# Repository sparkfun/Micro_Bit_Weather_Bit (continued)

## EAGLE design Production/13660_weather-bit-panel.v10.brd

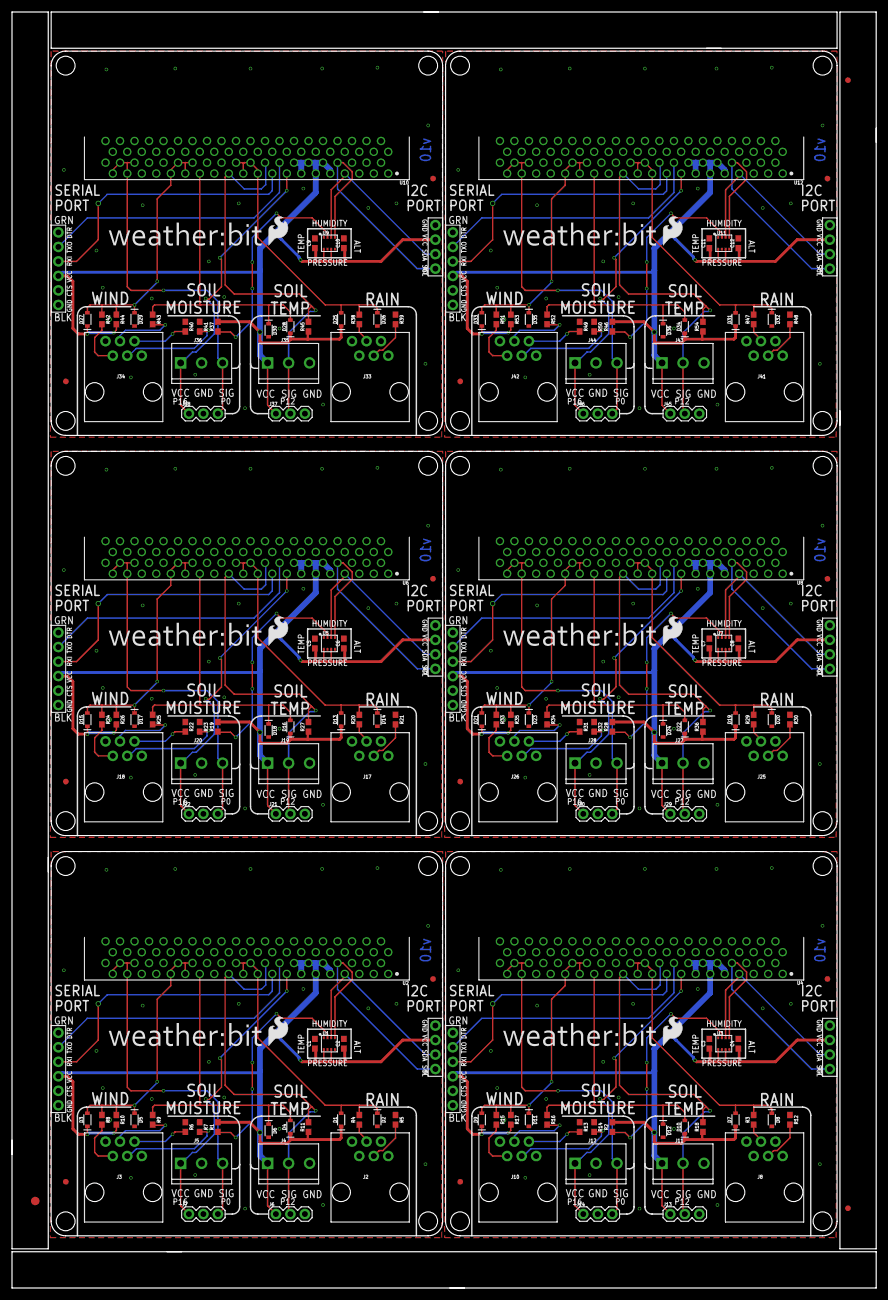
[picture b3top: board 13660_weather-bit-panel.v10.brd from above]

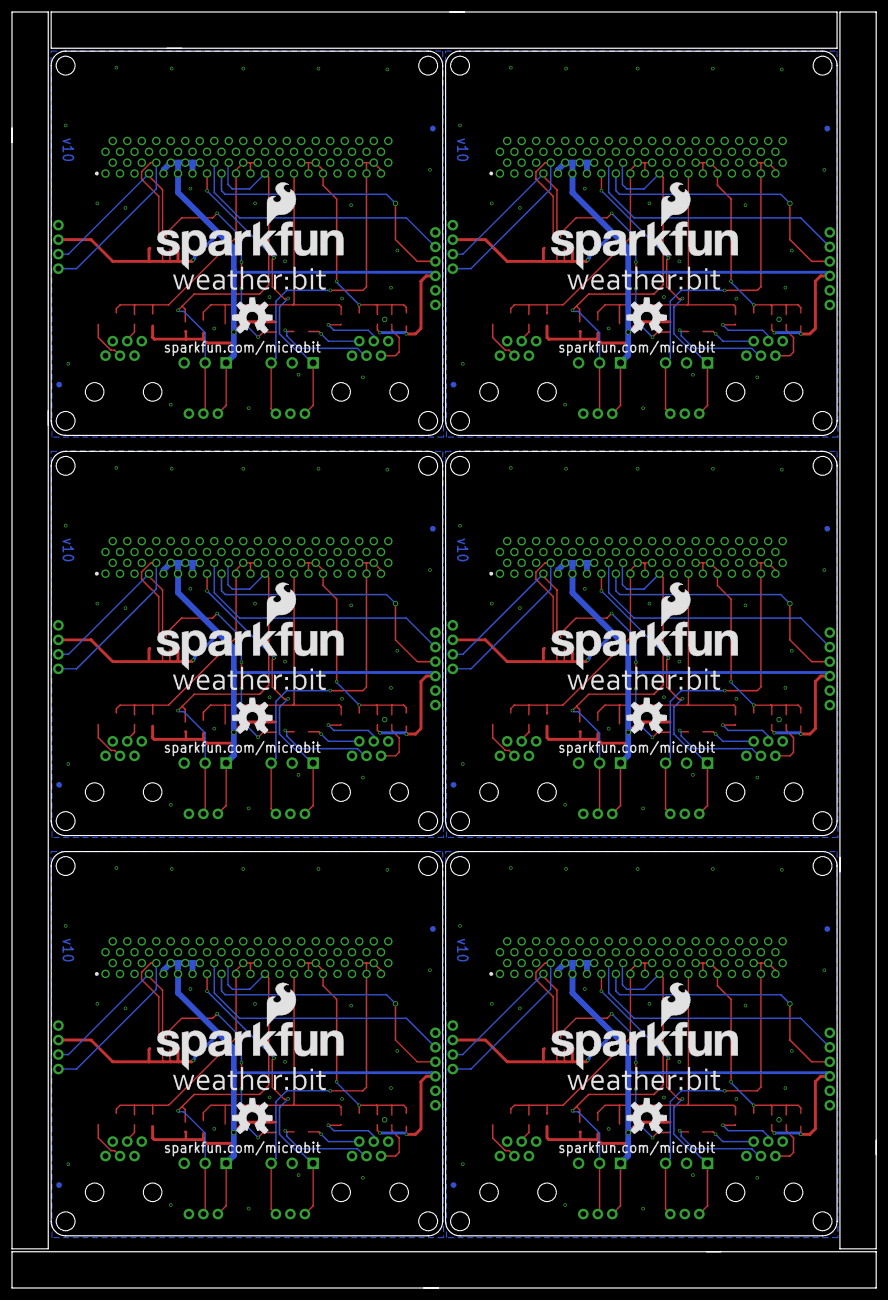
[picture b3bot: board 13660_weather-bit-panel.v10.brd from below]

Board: 2 copper layers, 151.4 x 223.5 mm, 243 parts (30 on the bottom side), 114 nets.

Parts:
C1, C2, C3, C4, C5, C6, C7, C8, C9, C10, C11, C12: 0.1uF; 0603
D1, D2, D3, D4, D5, D6, D7, D8, D9, D10, D11, D12, D13, D14, D15, D16, D17, D18, D19, D20, D21, D22, D23, D24, D25, D26, D27, D28, D29, D30, D31, D32, D33, D34, D35, D36: 250mA/100V; SOD-323
E$1: FIDUCIAL-1.5X3
E$7, E$8: FIDUCIAL-1X2
FD1, FD2, FD3, FD4, FD5, FD6, FD7, FD8, FD9, FD10, FD11, FD12, FD13, FD14, FD15, FD16, FD17, FD18, FD19, FD20, FD21, FD22, FD23, FD24: FIDUCIAL1X2; FIDUCIAL-1X2
H1, H2, H3, H4, H5, H6, H7, H8, H9, H10, H11, H12, H13, H14, H15, H16, H17, H18, H19, H20, H21, H22, H23, H24: STAND-OFF
J1, J16, J24, J32, J40, J48: 6_PIN_SERIAL_TARGET_SIDE_W_SILK
J2, J3, J8, J10, J17, J18, J25, J26, J33, J34, J41, J42: RJ11; RJ11-6
J4, J5, J11, J12, J19, J20, J27, J28, J35, J36, J43, J44: SCREWTERMINAL-3.5MM-3_LOCK.007S
J6, J7, J13, J14, J21, J22, J29, J30, J37, J38, J45, J46: 1X03
J9, J15, J23, J31, J39, J47: 1X04_NO_SILK
LOGO1, LOGO3, LOGO5, LOGO7, LOGO9, LOGO11: OSHW-LOGOL; OSHW-LOGO-L
LOGO2, LOGO4, LOGO6, LOGO8, LOGO10, LOGO12: SFE_LOGO_NAME_FLAME.3_INCH; SFE_LOGO_NAME_FLAME_.3
R1, R2, R10, R11, R17, R18, R19, R26, R27, R28, R35, R36, R37, R44, R45, R46, R53, R54: 4.7k; 0603
R3, R4, R5, R6, R7, R8, R9, R12, R13, R14, R15, R16, R20, R21, R22, R23, R24, R25, R29, R30, R31, R32, R33, R34, R38, R39, R40, R41, R42, R43, R47, R48, R49, R50, R51, R52: 1k; 0603
U1, U3, U5, U7, U9, U11: BME280; LGA-8-2.5X2.5
U2, U4, U6, U8, U10, U12: micro:bit; MICRO:BIT_RA_PTH
U$1, U$4, U$7, U$10, U$13, U$16: SFE_LOGO_FLAME_.2
U$2, U$3, U$5, U$6, U$8, U$9, U$11, U$12, U$14, U$15, U$17, U$18: LOGO-WEATHERBIT

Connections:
3.3V: C1.1, C2.1, D1.C, D3.C, D4.C, J1.P$4, J4.1, J6.1, J9.3, R1.2, R10.2, R11.1, U1.6, U1.8, U2.A9, U2.A10, U2.A11, U2.A12, U2.A13, U2.A14
3.3V1: C3.1, C4.1, D7.C, D9.C, D10.C, J11.1, J13.1, J15.3, J16.P$4, R2.2, R17.2, R18.1, U3.6, U3.8, U4.A9, U4.A10, U4.A11, U4.A12, U4.A13, U4.A14
3.3V2: C5.1, C6.1, D13.C, D15.C, D16.C, J19.1, J21.1, J23.3, J24.P$4, R19.2, R26.2, R27.1, U5.6, U5.8, U6.A9, U6.A10, U6.A11, U6.A12, U6.A13, U6.A14
3.3V3: C7.1, C8.1, D19.C, D21.C, D22.C, J27.1, J29.1, J31.3, J32.P$4, R28.2, R35.2, R36.1, U7.6, U7.8, U8.A9, U8.A10, U8.A11, U8.A12, U8.A13, U8.A14
3.3V4: C9.1, C10.1, D25.C, D27.C, D28.C, J35.1, J37.1, J39.3, J40.P$4, R37.2, R44.2, R45.1, U9.6, U9.8, U10.A9, U10.A10, U10.A11, U10.A12, U10.A13, U10.A14
3.3V5: C11.1, C12.1, D31.C, D33.C, D34.C, J43.1, J45.1, J47.3, J48.P$4, R46.2, R53.2, R54.1, U11.6, U11.8, U12.A9, U12.A10, U12.A11, U12.A12, U12.A13, U12.A14
GND: C1.2, C2.2, D2.A, D5.A, D6.A, J1.P$5, J1.P$6, J4.3, J5.2, J6.3, J7.2, J9.4, R5.1, R6.1, R7.1, U1.1, U1.5, U1.7, U2.A1, U2.A2, U2.A3, U2.A4, U2.A5, U2.A6
GND1: C3.2, C4.2, D8.A, D11.A, D12.A, J11.3, J12.2, J13.3, J14.2, J15.4, J16.P$5, J16.P$6, R12.1, R13.1, R14.1, U3.1, U3.5, U3.7, U4.A1, U4.A2, U4.A3, U4.A4, U4.A5, U4.A6
GND2: C5.2, C6.2, D14.A, D17.A, D18.A, J19.3, J20.2, J21.3, J22.2, J23.4, J24.P$5, J24.P$6, R21.1, R22.1, R23.1, U5.1, U5.5, U5.7, U6.A1, U6.A2, U6.A3, U6.A4, U6.A5, U6.A6
GND3: C7.2, C8.2, D20.A, D23.A, D24.A, J27.3, J28.2, J29.3, J30.2, J31.4, J32.P$5, J32.P$6, R30.1, R31.1, R32.1, U7.1, U7.5, U7.7, U8.A1, U8.A2, U8.A3, U8.A4, U8.A5, U8.A6
GND4: C9.2, C10.2, D26.A, D29.A, D30.A, J35.3, J36.2, J37.3, J38.2, J39.4, J40.P$5, J40.P$6, R39.1, R40.1, R41.1, U9.1, U9.5, U9.7, U10.A1, U10.A2, U10.A3, U10.A4, U10.A5, U10.A6
GND5: C11.2, C12.2, D32.A, D35.A, D36.A, J43.3, J44.2, J45.3, J46.2, J47.4, J48.P$5, J48.P$6, R48.1, R49.1, R50.1, U11.1, U11.5, U11.7, U12.A1, U12.A2, U12.A3, U12.A4, U12.A5, U12.A6
unnamed: R1.1, U1.2
unnamed: R2.1, U3.2
unnamed: J8.3, R3.1
unnamed: J2.3, R4.1
unnamed: J3.2, R8.2
unnamed: J2.4, R5.2
unnamed: J8.4, R12.2
unnamed: J10.3, R16.2
unnamed: J3.3, R9.2
unnamed: J10.5, R13.2
unnamed: J3.5, R6.2
unnamed: J3.4, R7.2
unnamed: J10.4, R14.2
unnamed: J10.2, R15.2
unnamed: R19.1, U5.2
unnamed: J17.3, R20.1
unnamed: J17.4, R21.2
unnamed: J18.3, R25.2
unnamed: J18.5, R22.2
unnamed: J18.4, R23.2
unnamed: J18.2, R24.2
unnamed: R28.1, U7.2
unnamed: J25.3, R29.1
unnamed: J25.4, R30.2
unnamed: J26.3, R34.2
unnamed: J26.5, R31.2
unnamed: J26.4, R32.2
unnamed: J26.2, R33.2
unnamed: R37.1, U9.2
unnamed: J33.3, R38.1
unnamed: J33.4, R39.2
unnamed: J34.3, R43.2
unnamed: J34.5, R40.2
unnamed: J34.4, R41.2
unnamed: J34.2, R42.2
unnamed: R46.1, U11.2
unnamed: J41.3, R47.1
unnamed: J41.4, R48.2
unnamed: J42.3, R52.2
unnamed: J42.5, R49.2
unnamed: J42.4, R50.2
unnamed: J42.2, R51.2
RAIN: D1.A, D2.C, R4.2, U2.A19, U2.A20, U2.A21, U2.A22
RAIN1: D7.A, D8.C, R3.2, U4.A19, U4.A20, U4.A21, U4.A22
RAIN2: D13.A, D14.C, R20.2, U6.A19, U6.A20, U6.A21, U6.A22
RAIN3: D19.A, D20.C, R29.2, U8.A19, U8.A20, U8.A21, U8.A22
RAIN4: D25.A, D26.C, R38.2, U10.A19, U10.A20, U10.A21, U10.A22
RAIN5: D31.A, D32.C, R47.2, U12.A19, U12.A20, U12.A21, U12.A22
RXI: J1.P$3, U2.A17
RXI1: J16.P$3, U4.A17
RXI2: J24.P$3, U6.A17
RXI3: J32.P$3, U8.A17
RXI4: J40.P$3, U10.A17
RXI5: J48.P$3, U12.A17
SCL: J9.1, U1.4, U2.A8
SCL1: J15.1, U3.4, U4.A8
SCL2: J23.1, U5.4, U6.A8
SCL3: J31.1, U7.4, U8.A8
SCL4: J39.1, U9.4, U10.A8
SCL5: J47.1, U11.4, U12.A8
SDA: J9.2, U1.3, U2.A7
SDA1: J15.2, U3.3, U4.A7
SDA2: J23.2, U5.3, U6.A7
SDA3: J31.2, U7.3, U8.A7
SDA4: J39.2, U9.3, U10.A7
SDA5: J47.2, U11.3, U12.A7
SOIL_DAT: J5.3, J7.3, U2.A36, U2.A37, U2.A38, U2.A39
SOIL_DAT1: J12.3, J14.3, U4.A36, U4.A37, U4.A38, U4.A39
SOIL_DAT2: J20.3, J22.3, U6.A36, U6.A37, U6.A38, U6.A39
SOIL_DAT3: J28.3, J30.3, U8.A36, U8.A37, U8.A38, U8.A39
SOIL_DAT4: J36.3, J38.3, U10.A36, U10.A37, U10.A38, U10.A39
SOIL_DAT5: J44.3, J46.3, U12.A36, U12.A37, U12.A38, U12.A39
SOIL_PWR: J5.1, J7.1, U2.A15
SOIL_PWR1: J12.1, J14.1, U4.A15
SOIL_PWR2: J20.1, J22.1, U6.A15
SOIL_PWR3: J28.1, J30.1, U8.A15
SOIL_PWR4: J36.1, J38.1, U10.A15
SOIL_PWR5: J44.1, J46.1, U12.A15
TEMP_DAT: J4.2, J6.2, R11.2, U2.A18, U2.A23
TEMP_DAT1: J11.2, J13.2, R18.2, U4.A18, U4.A23
TEMP_DAT2: J19.2, J21.2, R27.2, U6.A18, U6.A23
TEMP_DAT3: J27.2, J29.2, R36.2, U8.A18, U8.A23
TEMP_DAT4: J35.2, J37.2, R45.2, U10.A18, U10.A23
TEMP_DAT5: J43.2, J45.2, R54.2, U12.A18, U12.A23
TXO: J1.P$2, U2.A16
TXO1: J16.P$2, U4.A16
TXO2: J24.P$2, U6.A16
TXO3: J32.P$2, U8.A16
TXO4: J40.P$2, U10.A16
TXO5: J48.P$2, U12.A16
WDIR: D3.A, D5.C, R8.1, R10.1, U2.A28, U2.A29, U2.A30, U2.A31
WDIR1: D9.A, D11.C, R15.1, R17.1, U4.A28, U4.A29, U4.A30, U4.A31
WDIR2: D15.A, D17.C, R24.1, R26.1, U6.A28, U6.A29, U6.A30, U6.A31
WDIR3: D21.A, D23.C, R33.1, R35.1, U8.A28, U8.A29, U8.A30, U8.A31
WDIR4: D27.A, D29.C, R42.1, R44.1, U10.A28, U10.A29, U10.A30, U10.A31
WDIR5: D33.A, D35.C, R51.1, R53.1, U12.A28, U12.A29, U12.A30, U12.A31
WSPEED: D4.A, D6.C, R9.1, U2.A27
WSPEED1: D10.A, D12.C, R16.1, U4.A27
WSPEED2: D16.A, D18.C, R25.1, U6.A27
WSPEED3: D22.A, D24.C, R34.1, U8.A27
WSPEED4: D28.A, D30.C, R43.1, U10.A27
WSPEED5: D34.A, D36.C, R52.1, U12.A27

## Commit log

2017-03-20 Initial Commit to set up repo
2017-03-23 Sch and Brd files initial commit
2017-03-27 Updated Baord Layout, prepping for today's meeting
2017-03-29 Updated brd and sch file 3/28/2017
2017-03-29 updated board and sch files 3/29
2017-03-30 Adding Library Part Updated Brd File Updated Sch File 3/30/2017
2017-04-03 Updated BRD and SCH files per Design Review 3/31
2017-04-06 Updated brd and sch files per QC Review
2017-04-10 Updated BRD and SCH files per EDU
2017-04-11 replacing proportional font back to vector font
2017-04-18 updated weather:bit Logo
2017-04-18 Updated logo info
2017-04-20 Updated silk per review 4/19
2017-05-23 Updated One-Wire Hardware Set-up
2017-05-31 Updating weather:bit per QC review
2017-05-31 Updated text in sch
2017-05-31 panel
2017-07-21 updating file structure for product release - adding notes to readme
2019-01-08 micro:arcade Example Code HEX files
    Add compiled MakeCode example code used in kit.
2019-02-08 Update microbit-Weather-Bit-Experiment-7-OpenLog.hex
    Updated code with button press to begin logging and to pause logging. It's a hex file but you can still import it in MakeCode to view code.
2019-02-08 Update microbit-Weather-Bit-Experiment-7-OpenLog.hex
    Update code again for a better user experience. There was a weird debounce after pressing the button the first time. =)
2019-10-30 Added qwiic connector and logos
    - added vertical qwiic connector near the 4-pin I2C header
    - added qwiic logo near connector
    - added big qwiic logos near product names on top and bottom silk
2019-10-30 SMD connector on 40 pin RA, and 4-pin I2C header
2019-10-31 Moved to SMT vertical female header for Serial port
2019-10-31 SMT serial header and buzzard silk update
2019-10-31 sch cleanup and move to one sheet
2019-10-31 PROD_ID on serial header SMT vertical
2019-10-31 run of checklist
    - vector font in sch
    - added testpoints
    - corrected measures
2019-11-04 switched to TIGHT DRC, nudging and routing
    -updated package on 4-pin SMD to allow for routing to either pad under each header
    -moved to TIGHT DRC, some slight nudging of routes to comply
    -rotated SERIAL PORT silk to match pin labels
2019-11-05 Finalized test points and test point positions
2019-11-05 gerbers for proto order
2019-12-10 Connected TEMP_DATA to P13
    On v10, TEMP_DATA was connected to both P12 and P13 (for the one-wire interface to the temp sensor).
    v11 only had TEMP_DATA connected to P12.
    With this commit (v12), TEMP_DATA is connected to both P12 and P13 (to match the original v10).
    Also incremented version to v12 in BRD and SCH.
2019-12-13 Production panel v12
2020-01-30 Update readme - product image and link
2020-01-30 update readme - forum link
2020-01-30 update readme - product name to new name
2020-02-03 Update for MakeCode V1
    MakeCode Editor v1 does floating point arithmetic now and will output several decimal places on the LED display. Updated examples to prevent user from waiting until the data finishes scrolling.
    - update exp 1 to simply output integer using integer division block
    - update exp 4 to simply output integer using integer division block
    - update exp 5 to truncate the output to output integer with the option to view the output on the MakeCode Console
    - update exp 6 animation to read easier, round the output, and option to view data on the MakeCode Console
2020-05-11 Add Wireless Examples
